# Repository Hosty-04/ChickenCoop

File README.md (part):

# Kurník

Systém pro automatizaci kurníku s detekcí snesených vajec - bakalářská práce

## Zadání

- Prostudujte možnosti automatizace uzavírání kurníku, možné metody detekce snesených vajec a dostupné možnosti komunikace a připojení zařízení do IoT sítě (např. NB-IoT, WiFi, LoRaWAN).
- Navrhněte systém pro automatické otevírání a uzavírání dvířek kurníku s možností rozšíření o jednotky se senzory ve snáškových hnízdech (min. 5 hnízd). Prostudujte možnosti napájení z akumulátoru nebo fotovoltaického panelu. Proveďte analýzu možnosti přenosu dat do cloudu a jejich zobrazení uživateli včetně historie snášek a možnosti vzdáleného ovládání, například skrze aplikaci.
- Na základě analýzy navrhněte způsob vzdálené uživatelské interakce pro zobrazení stavu dvířek, manuální ovládání a počítání snesených vajec.
- Navrhněte schéma zařízení, které bude obsahovat mikrořadič, komunikační modul, senzory, řízení dvířek, napájecí/nabíjecí obvody. Dbejte na nízký příkon celého zařízení. Proveďte návrh desky plošných spojů.
- Zkonstruujte hardwarovou realizaci navrženého systému. Osaďte a zprovozněte řídicí elektroniku. Vytvořte ovládací firmware. Realizujte přenos dat ze zařízení k uživateli včetně ovládacího rozhraní a možnosti zobrazení historie.
- Ověřte funkčnost systému experimentálním měřením a vyhodnoťte spolehlivost detekce a ovládání.
- Zveřejněte veškeré výrobní podklady na vhodné platformě (např. GitHub).

## Schémata

## Elektronika

<br>

<picture>
  <source media="(prefers-color-scheme: dark)" srcset="Schematics/block_schematic_electronics_white.png">
  <source media="(prefers-color-scheme: light)" srcset="Schematics/block_schematic_electronics_black.png">
  
</picture>

## Komunikace

<br>

<picture>
  <source media="(prefers-color-scheme: dark)" srcset="Schematics/block_schematic_comms_white.png">
  <source media="(prefers-color-scheme: light)" srcset="Schematics/block_schematic_comms_black.png">
  
</picture>

<br><br>

> Uživatelské příkazy cestují opačným směrem

## Popis

### 1) Mechanika

### a) Krabičky

Solární panel je uchycen v rámečku vytištěném z materiálu PETG, jehož vnější rozměr (360 × 240 mm) přesahuje rozměr panelu (340 × 220 mm) o 10 mm po každé straně. Tento materiál byl zvolen pro jeho vysokou houževnatost a teplotní odolnost. Kapsa pro panel je hluboká 4 mm, tedy o 1 mm více než tloušťka panelu, aby panel po vložení mírně zapadl pod úroveň okraje rámečku a nedocházelo k zadržování vody na jeho povrchu. Dno kapsy je opatřeno výřezem o rozměru 320 × 200 mm, odpovídajícím aktivní ploše panelu, takže rámeček má tvar pasparty a nestíní dopadající sluneční záření. Po vložení panelu do kapsy je spára mezi jeho okrajem a stěnou rámečku vyplněna venkovním UV odolným silikonovým tmelem, čímž vzniká vodotěsné a zároveň mechanicky pevné spojení bez nutnosti vrtat do samotného panelu. Rámeček je přišroubován přímo ke stěně kurníku vruty 6 × 80 mm s plastovými hmoždinkami 8 mm, a to přes čtyři otvory o průměru 5 mm v rozích mimo aktivní plochu panelu.

Konstrukce obsahuje jednu krabičku pro akumulátor o tloušťce stěny 2,4 mm a jednu krabičku (K) o tloušťce stěny 1,6 mm určenou pro mechaniku a elektroniku dvířek a hlavní mikrořadič. Pro každé snáškové hnízdo je dále vyhrazena samostatná krabička (Kx) se stejnou tloušťkou stěny, obsahující potřebnou elektroniku a hnízdový mikrořadič. Všechny krabičky jsou vytištěny na 3D tiskárně z materiálu PETG. Do tohoto materiálu je kvůli riziku deformace nutné vrtat při nízkých otáčkách. Zadní stěna krabiček je ve svislém směru prodloužena a má tloušťku 3,5 mm; v každém rohu této stěny jsou otvory pro vruty 4 × 40 mm, které umožňují upevnění krabiček k betonové stěně kurníku pomocí hmoždinek o průměru 6 mm. Víko je vytištěno samostatně s přesahem 2 mm; uprostřed jeho levé hrany je dutá trubička s vnitřním průměrem 2 mm. Stejná trubička je u všech krabiček na obou koncích vnější horní hrany levé stěny. Po vytištění je všemi třemi trubičkami protažen filament o průměru 1,75 mm, jehož konce se krátce nahřejí zapalovačem a roztepou do podoby hlaviček. Tím vzniká jednoduchý pant pro uchycení víka.

V krabičkách K a Kx jsou desky plošných spojů připevněny ke dnu pomocí montážních děr (hlavní i hnízdová deska po 3), šrouby vedou zeshora přes distanční sloupky a jsou zajištěny maticí. U víka krabiček jsou vytvořeny nízké drážky ve tvaru písmene U s mírně zaoblenými rohy, sloužící k protažení kabelů. Pro kabel o průřezu 1,5 mm² mají šířku 4,5 mm, hloubku 3 mm a zaoblení dna i hran 1 mm; pro kabel o průřezu 0,5 mm² šířku 3,5 mm, hloubku 2 mm a zaoblení dna i hran 0,75 mm; pro datový kabel pak šířku 6 mm, hloubku 3,5 mm a stejné zaoblení jako u prvního kabelu. Krabička pro akumulátor má zespodu dva kruhové otvory o průměru 5 mm určené pro průchod napájecích kabelů a dva větrací otvory o průměru 4 mm, umístěné v horní a spodní části tak, aby mohl uvnitř cirkulovat vzduch. Krabička Kx má zespodu jeden podlouhlý otvor 6 × 2 mm se zaoblenými konci pro průchod 4 vodičů plochého kabelu DS1058 s roztečí 1,27 mm, které prodlužují vodiče tenzometru (pásek 4 vodičů je široký 5,08 mm a tlustý asi 1 mm), krabička K pak ručně vyvrtaný a zakulacený otvor o průměru 4 mm pro lanko; anténa bude položená horizontálně uvnitř krabičky.

### b) Kabeláž

Pro připojení solárního panelu a akumulátoru je použita měděná ohebná licna o průřezu 1,5 mm², připojená přes 4pinovou pružinovou WAGO svorkovnici s roztečí 5,08 mm k desce plošných spojů. Tento průřez poskytuje dostatečnou proudovou rezervu při minimálním úbytku napětí. Stejným způsobem, avšak za využití licny o průřezu 0,5 mm², jsou k desce plošných spojů připojeny mikrospínače. Motor je u finální verze přes držák připevněn přímo k hlavní desce plošných spojů; u prototypu je připojen licnou o průřezu 0,5 mm² přes 2pinovou svorkovnici.

Pro datovou komunikaci byl zvolen kabel UTP CAT5e typu licna, jehož kroucené páry omezují rušení. K deskám plošných spojů je připojený přes konektory RJ45. Prodloužení vodičů tenzometru o průřezu 0,08 mm² zajišťují 4 vodiče plochého kabelu DS1058 (rozteč 1,27 mm) o stejné barvě a průřezu. Spojeny jsou pájkou a přes každý spoj je převlečena smršťovací bužírka s lepidlem o poměru 3:1 a rozměru 3 mm / 1 mm. K desce plošných spojů jsou připojeny přes 4pinovou pružinovou WAGO svorkovnici 233-504 s roztečí 2,54 mm (1 = E− (GND), 2 = E+ (AVDD), 3 = A− (IN−), 4 = A+ (IN+)).

Kabely a vodiče jsou vedeny v klasické elektroinstalační PVC liště o rozměrech 15 × 10 mm, upevněné k betonové stěně, respektive základové desce, pomocí vrutů 3 × 30 mm a hmoždinek o průměru 5 mm. Spoje jsou utěsněny akrylovým tmelem. Speciální UV odolná lišta není pro kabely vedené po venkovní stěně kurníku potřeba, protože tato stěna je vystavena slunci pouze při jeho západu. Životnost běžné lišty se odhaduje na 5–10 let.

U prototypu jsou využity stejné kabely, vodiče a svorkovnice. Na rozdíl od finální verze jsou ale využity drátky do nepájivého pole o průřezu 0,5 mm², který plně vyhovuje proudovému odběru systému.

### c) Konstrukce

Hlavní část systému je umístěna na vnější stěně kurníku, která splňuje požadavky na umístění solárního panelu popsané v kapitole Napájení. Toto řešení zjednodušuje montáž a zároveň z velké části eliminuje vliv amoniaku ze slepičího trusu na elektroniku.

Na betonovou stěnu jsou pomocí vrutů a hmoždinek připevněny svislé dřevěné hranolky, k jejichž bočním stěnám jsou vruty upevněny hliníkové U-profily se šířkou dna 15 mm, výškou bočních stěn 15 mm, tloušťkou 1,5 mm a délkou 1 m. První vrut je umístěn na horní pozici, nad kterou se dvířka nikdy nedostanou, a druhý vrut na dolní pozici, kam dvířka nikdy nedojedou. U-profily zajišťují přesné vedení dvířek při minimálním tření. V těchto profilech se ve svislém směru pohybují nalakovaná pěněná PVC dvířka o rozměrech 24 × 35 cm a tloušťce 8 mm (pozor na výrobní tolerance). Hmotnost těchto dvířek je 350 g. Při vrtání otvorů do PVC je nutné použít nízké otáčky a nevyvíjet nadměrný přítlak. Pěněné PVC bylo zvoleno pro nízkou hmotnost, odolnost proti vlhkosti a snadnou obrobitelnost.

V horní i dolní části hranolku jsou ve svislé ose zapuštěny dva pákové koncové spínače sledující polohu dvířek. Záhlubení široká 6,5 mm a vysoká 20 mm z vnitřní strany a 15 mm z vnější strany vedou skrz hranolek a 10 mm širokou hliníkovou drážku; z vnější strany jsou kabely vyvedeny přímo do lišty. Spínače jsou upevněny vruty o průměru 2 mm. Toto provedení představuje jednoduché řešení určování krajních poloh dvířek.

Na horní části přední strany dvířek je umístěno závěsné očko M5 z nerezové oceli A2, upevněné podložkou a samojistnou maticí ze stejného materiálu; očko prochází otvorem o průměru odpovídajícím jeho metrickému závitu. Očkem je protaženo syntetické lanko (zednická šňůra) o průměru 2 mm, zajištěné dračí smyčkou zakápnutou vteřinovým lepidlem. Syntetická šňůra nekoroduje, má nízkou průtažnost a je odolná vůči vlhkosti.

Lanko vede kolmo vzhůru do krabičky K, kde je navíjeno na špulku vytištěnou z materiálu PETG (šířka 2 cm, vnější průměr 2,5 cm). Lanko je provlečeno otvorem o průměru 3 mm na okraji špulky (na straně vzdálenější od motoru) a zajištěno osmičkovým uzlem, rovněž zakápnutým vteřinovým lepidlem; uzel je zapuštěn 8 mm hluboko do záhlubení o průměru 10 mm a lanko z něj vychází na okraji záhlubení směrem k okraji špulky.

Špulka má otvor s D-profilem (průměr 3 mm, hloubka 10 mm); pomocí stavěcího šroubu (červíku) M5 z nerezové oceli A4 (délka 6 mm) a mosazné závitové vložky M5 (délka 5,8 mm, průměr 7,1 mm) je upevněna na hřídeli nízkootáčkového (20 rpm) stejnosměrného motoru s kovovou převodovkou (6 V), a to ze strany, kde vstupuje lanko. Stejnosměrný motor s převodovkou byl zvolen místo krokového motoru, protože vystačí s jednoduchým budičem, převodovka mu dává vysoký krouticí moment a polohu dvířek určují koncové spínače, takže není potřeba počítat kroky. U finální verze bude motor přes držák připevněn k hlavní desce plošných spojů.

<br>

**Tah motoru pro různé krouticí momenty**

$$
M = F \cdot r
$$

$$
F_j = \frac{M_j}{r_s} = \frac{5\ \text{N·cm}}{12,5\ \text{mm}} = 4\ \text{N} \approx \mathbf{400\ \text{g tahu}}
$$

$$
F_d = \frac{M_d}{r_s} = \frac{4\ \text{N·cm}}{12,5\ \text{mm}} = 3,2\ \text{N} \approx \mathbf{320\ \text{g tahu}}
$$

$$
F_k = \frac{M_k}{r_s} = \frac{25\ \text{N·cm}}{12,5\ \text{mm}} = 20\ \text{N} \approx \mathbf{2\ \text{kg tahu}}
$$

kde:

- $F_j$ ... síla při jmenovitém krouticím momentu
- $F_d$ ... síla při doporučeném dlouhodobém trvalém zatížení
- $F_k$ ... síla při maximálním krátkodobém zatížení
- $M_j$ ... jmenovitý krouticí moment
- $M_d$ ... krouticí moment při doporučeném dlouhodobém trvalém zatížení
- $M_k$ ... krouticí moment při maximálním krátkodobém zatížení
- $r_s$ ... poloměr špulky

Dvířka o hmotnosti 350 g představují mírně vyšší zátěž, než je doporučené trvalé zatížení, tudíž lze očekávat pokles otáček motoru na 15–17 ot./min. Počítá se i s rezervou pro případ mírného drhnutí dvířek v drážkách. Nízkootáčkový motor spolu s menším vnějším průměrem špulky byl zvolen pro zvýšení síly motoru a snížení rizika přetrhnutí lanka nebo vykolejení dvířek.

<br>

Otvor pro mosaznou závitovou vložku má průměr 8 mm a v posledních 6,5 mm směrem ke hřídeli se zužuje na 6,5 mm. Vložka se do otvoru zavede pomocí 16mm šroubu M5; jakmile narazí na zúženou část otvoru, hlava šroubu se nahřeje mikropájkou, plast se v místě zúžení roztaví a umožní zalisování vložky. Po odejmutí pájky plast opět ztuhne a vložku pevně ukotví.

Vedlejší část systému tvoří spádovaná snášková hnízda s košíkem, orientovaná příčně ke stěně. Celá konstrukce musí být od stěny vzdálena natolik, aby se jí nikde nedotýkala a zároveň za ní zůstal prostor pro vedení kabelu. Návrh je koncipován tak, aby se do prostoru s tenzometrem nemohli dostat ani ti nejmenší hlodavci — rozměr základové desky a výška lišt jsou klíčové.

Pod hnízda je vruty (na vyšší straně hnízda přes dřevěné kvantlíky) připevněna voděodolná OSB 3 deska o rozměrech 37 × 28 cm a tloušťce 12 mm. Další deska (37-1,2-0,2 × 28-1,2-0,2 cm, stejná tloušťka) tvoří základovou desku a je připevněna k podlaze kurníku; třetí deska stejné tloušťky, o rozměrech 40 × 50 cm, slouží jako zadní stěna. Řezné hrany desek jsou natřeny lakem. Mezi horní a spodní deskou je u stěny umístěn tenzometr o tloušťce 12,7 mm, orientovaný kratší stranou s vodiči směrem ke stěně. Tenzometr váží s přesností 2 g, což pro vejce o hmotnosti 50–70 g plně postačuje, a je dimenzován na zatížení 20 kg — maximální předpokládané zatížení (dvě desky, hnízdo, dvě slepice a deset vajec) přitom činí přibližně 10 kg. Volný i pevný konec tenzometru je upevněn dvěma zápustnými imbusovými šrouby M5 z nerezové oceli A2, procházejícími vážicí, respektive základovou deskou skrz otvory o průměru 4,5 mm a zapuštěnými do záhlubení o průměru 10 mm a hloubce 3 mm; hlava šroubu je u vážicí desky zalita akrylovým tmelem. Použité šrouby mají délku 25 mm. Mezi deskami a závity tenzometru jsou umístěny distanční matice M6 z nerezové oceli A2 o tloušťce 4 mm.

Optická závora není pro počítání vajec v kurníku vhodná mimo jiné kvůli prachu, peří, podestýlce a zvědavým slepicím, jejichž přítomnost by mohla přerušit laserový paprsek a být chybně vyhodnocena jako propadnuté vejce. Z tohoto důvodu byl pro detekci vajec zvolen tenzometr.

Ze zbytku OSB desky jsou vyrobeny ochranné lišty, přišroubované zeshora po bocích základové desky. Lišty jsou vysoké 21,5 mm, protože vzdálenost mezi deskami činí 20,7 mm a celá horní konstrukce musí být podepřena pouze tenzometrem — zároveň musí zůstat zachována vůle alespoň 3 mm. Do zadní lišty je vyvrtán otvor, kterým prochází již prodloužený kabel od tenzometru; kabel nesmí být mechanicky namáhán tahem. Kabel dále vede vzhůru po stěně do krabičky Kx, odkud je z boku vyveden datový kabel, vedoucí vysoko po stěně až do krabičky K. Uprostřed konstrukce, naproti košíku, je vytvořen stavitelný doraz pomocí zápustného imbusového šroubu M5 z nerezové oceli A2 (délka 30 mm), procházejícího spodní deskou skrz otvor o průměru 4,5 mm a zapuštěného do záhlubení o průměru 10 mm a hloubce 6 mm. Doraz tvoří mosazná kloboučková matice M5 (délka 10 mm, délka závitu 7,5 mm), zvolená kvůli omezení ulpívání nečistot. Optimální vůle dorazu je 0,8 mm, což odpovídá jedné otáčce šroubu M5 nebo přibližně tloušťce běžné platební karty.

### 2) Řízení

Hlavní řídicí jednotkou systému je mikrořadič LoRa-E5 mini (M) se STM32WLE5JC a integrovaným LoRa modulem, komunikujícím přes LoRaWAN stack. Technologie LoRaWAN umožňuje na rozdíl od Wi-Fi komunikaci na velké vzdálenosti při nízké spotřebě energie a na rozdíl od NB-IoT trvalé řešení s dobrým pokrytím. U každého snáškového hnízda je umístěn úsporný mikrořadič STM32 NUCLEO-L031K6 (Mx); vlastní řadič v každém hnízdě zkracuje citlivé analogové vedení od tenzometru a usnadňuje přidání dalších hnízd. K programování slouží programátor ST-Link V2. Před programováním je potřeba programátor připojit k dané desce klasickými kabely DuPont — stačí propojit piny 3V3, SWCLK, SWDIO, GND a nRST. U finální verze jsou desky osazeny v paticích (dutinkových lištách); patice LoRa-E5 mini jsou vysoké 8,5 mm, takže pod modulem jsou na hlavní desce nízké SMD součástky a deska měří jen 81,5 × 40 mm. Stejně je řešena hnízdová deska: NUCLEO-L031K6 sedí v paticích 8,5 mm a pod ním jsou nízké SMD součástky. Vstupní konektor RJ45 je v levém horním rohu a vede kabel levou hranou, výstupní je v pravém horním rohu a vede kabel pravou hranou, svorkovnice tenzometru je u pravého okraje pod výstupním konektorem (horní hranou lícuje s horní hranou NUCLEO-L031K6) a deska měří 74 × 42 mm.

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
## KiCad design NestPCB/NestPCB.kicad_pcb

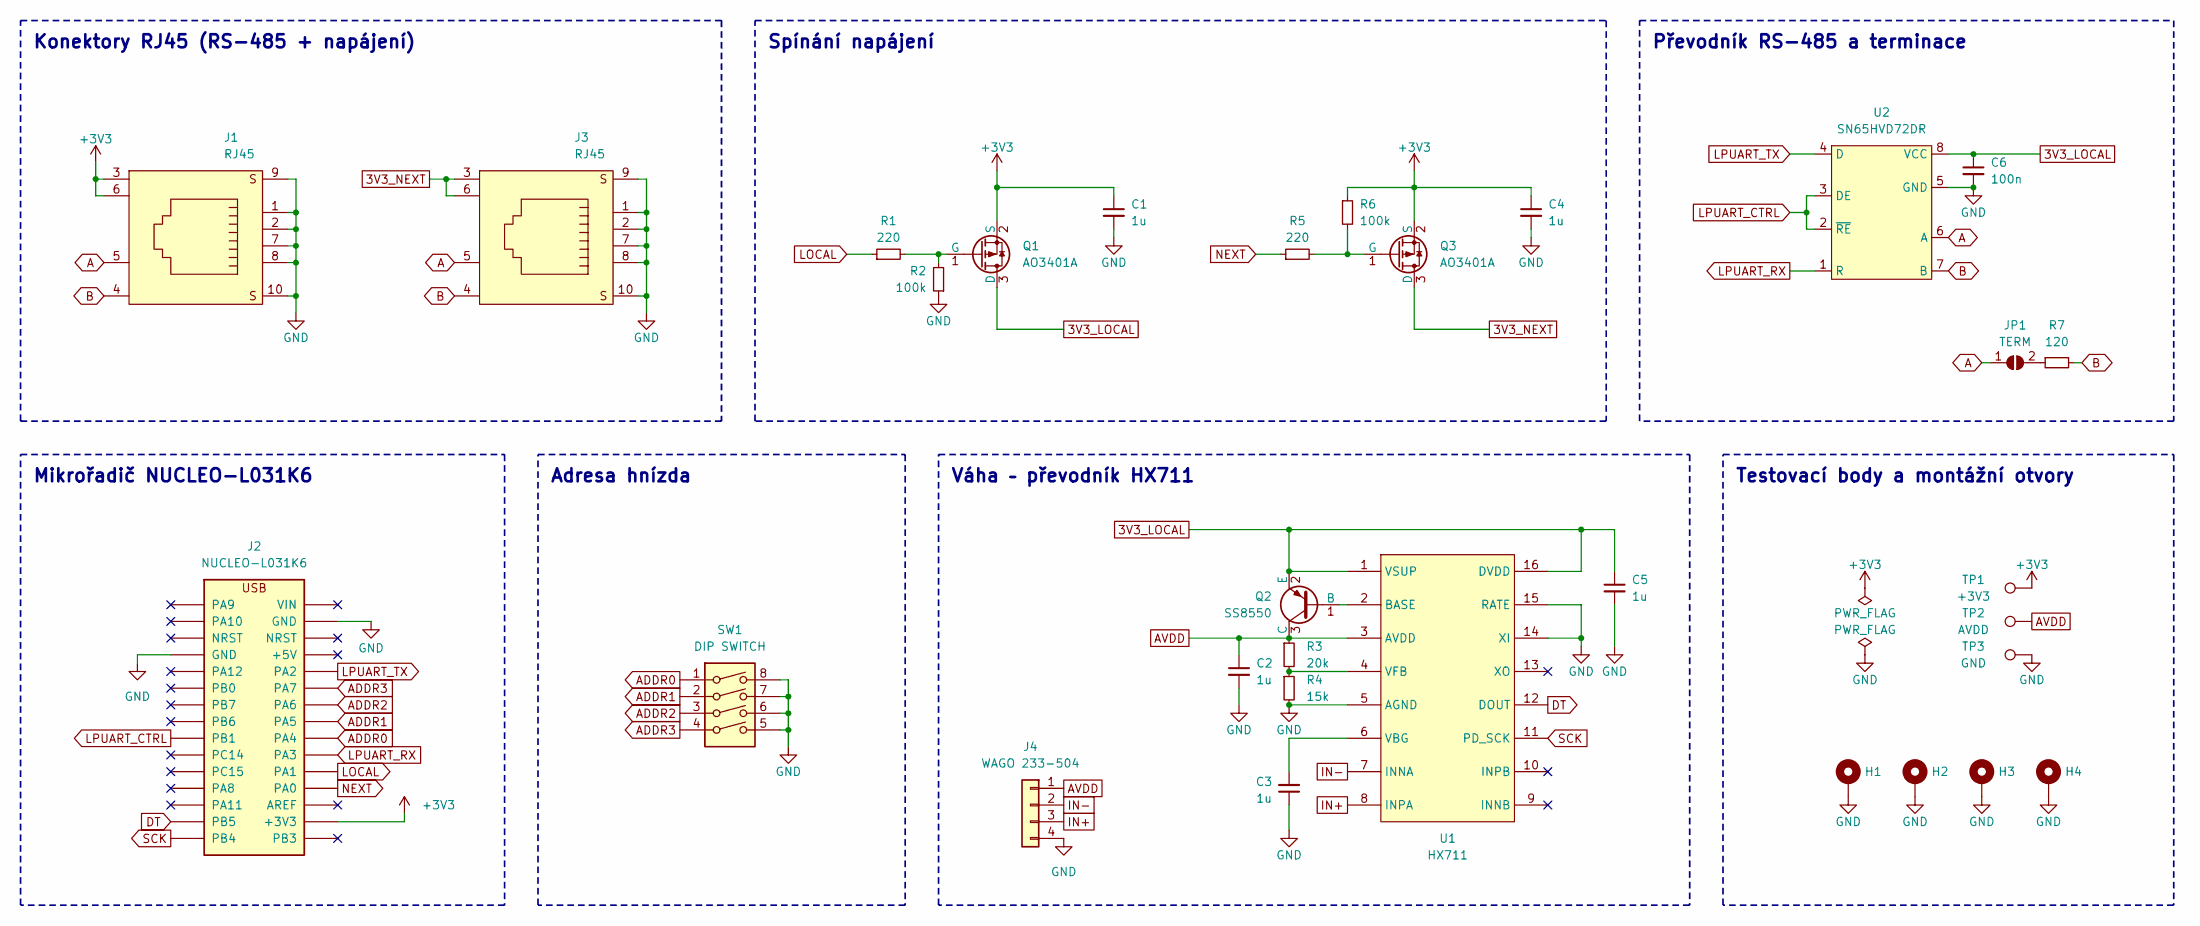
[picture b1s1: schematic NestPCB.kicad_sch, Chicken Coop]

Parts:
C1, C2, C3, C4, C5: 1u; C_0805_2012Metric
C6: 100n; C_0805_2012Metric
H1, H2, H3, H4: MountingHole_Pad; MountingHole_3.2mm_M3_Pad
J1, J3: RJ45; RJ45-TH_R-RJ45R08P-B000; LCSC Part C386756
J2: NUCLEO-L031K6
J4: WAGO 233-504; CONN-TH_233-504; LCSC Part C3309010
JP1: TERM; SolderJumper-2_P1.3mm_Open_RoundedPad1.0x1.5mm
Q1, Q3: AO3401A; SOT-23_L2.9-W1.3-P1.90-LS2.4-BR; LCSC Part C15127
Q2: SS8550; SOT-23_L2.9-W1.3-P1.90-LS2.4-BR; LCSC Part C8542
R1, R5: 220; R_0805_2012Metric
R2, R6: 100k; R_0805_2012Metric
R3: 20k; R_0805_2012Metric
R4: 15k; R_0805_2012Metric
R7: 120; R_0805_2012Metric
SW1: DIP SWITCH; SW-TH_DS-04XP; LCSC Part C319060
TP1: +3V3; TestPoint_THTPad_D2.0mm_Drill1.0mm
TP2: AVDD; TestPoint_THTPad_D2.0mm_Drill1.0mm
TP3: GND; TestPoint_THTPad_D2.0mm_Drill1.0mm
U1: HX711; SOP-16_L10.0-W3.9-P1.27-LS6.0-BL; LCSC Part C43656
U2: SN65HVD72DR; SOIC-8_L4.9-W3.9-P1.27-LS6.0-BL; LCSC Part C48125

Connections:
3V3_LOCAL: C5.1, C6.1, Q1.3 (D), Q2.2 (E), U1.1 (VSUP), U1.16 (DVDD), U2.8 (VCC)
3V3_NEXT: J3.3, J3.6, Q3.3 (D)
+3V3: C1.1, C4.1, J1.3, J1.6, J2.CN4-14 (+3V3), Q1.2 (S), Q3.2 (S), R6.1, TP1.1
A: J1.5, J3.5, JP1.1 (A), U2.6 (A)
ADDR0: J2.CN4-9 (PA4), SW1.1
ADDR1: J2.CN4-8 (PA5), SW1.2
ADDR2: J2.CN4-7 (PA6), SW1.3
ADDR3: J2.CN4-6 (PA7), SW1.4
AVDD: C2.1, J4.1, Q2.3 (C), R3.1, TP2.1, U1.3 (AVDD)
B: J1.4, J3.4, R7.2, U2.7 (B)
DT: J2.CN3-14 (PB5), U1.12 (DOUT)
GND: C1.2, C2.2, C3.1, C4.2, C5.2, C6.2, H1.1, H2.1, H3.1, H4.1, J1.1, J1.2, J1.7, J1.8, J1.9 (S), J1.10 (S), J2.CN3-4 (GND), J2.CN4-2 (GND), J3.1, J3.2, J3.7, J3.8, J3.9 (S), J3.10 (S), J4.4, R2.1, R4.2, SW1.5, SW1.6, SW1.7, SW1.8, TP3.1, U1.5 (AGND), U1.14 (XI), U1.15 (RATE), U2.5 (GND)
IN+: J4.3, U1.8 (INPA)
IN-: J4.2, U1.7 (INNA)
LOCAL: J2.CN4-11 (PA1), R1.1
LPUART_CTRL: J2.CN3-9 (PB1), U2.2 (~RE), U2.3 (DE)
LPUART_RX: J2.CN4-10 (PA3), U2.1 (R)
LPUART_TX: J2.CN4-5 (PA2), U2.4 (D)
NEXT: J2.CN4-12 (PA0), R5.1
unnamed: JP1.2 (B), R7.1
unnamed: Q1.1 (G), R1.2, R2.2
unnamed: Q2.1 (B), U1.2 (BASE)
unnamed: Q3.1 (G), R5.2, R6.2
unnamed: C3.2, U1.6 (VBG)
unnamed: R3.2, R4.1, U1.4 (VFB)
SCK: J2.CN3-15 (PB4), U1.11 (PD_SCK)

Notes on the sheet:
Váha – převodník HX711
Převodník RS-485 a terminace
Mikrořadič NUCLEO-L031K6
Testovací body a montážní otvory
Spínání napájení
Adresa hnízda
Konektory RJ45 (RS-485 + napájení)

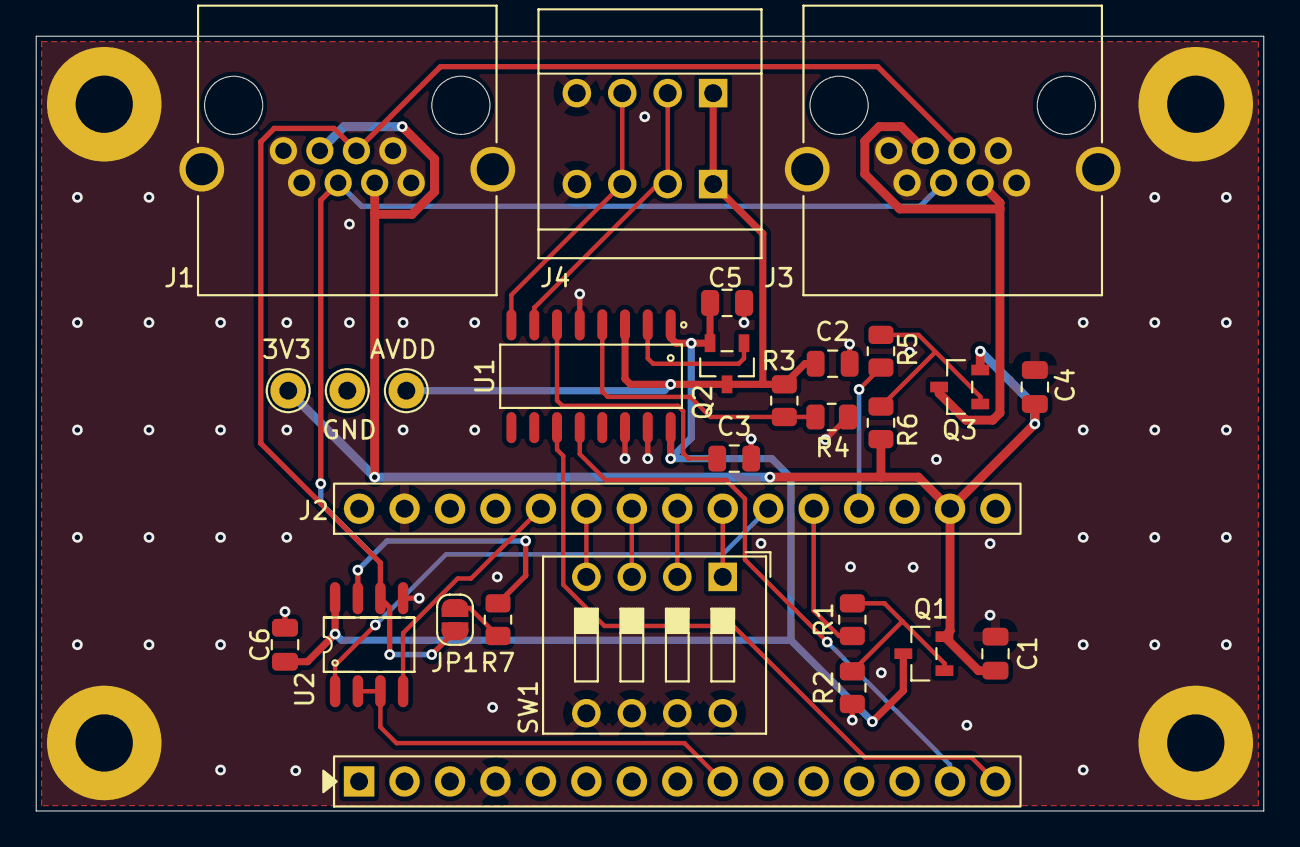
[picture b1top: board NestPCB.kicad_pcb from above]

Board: 2 copper layers, 68.6 x 43.3 mm, 31 parts (0 on the bottom side), 26 nets.

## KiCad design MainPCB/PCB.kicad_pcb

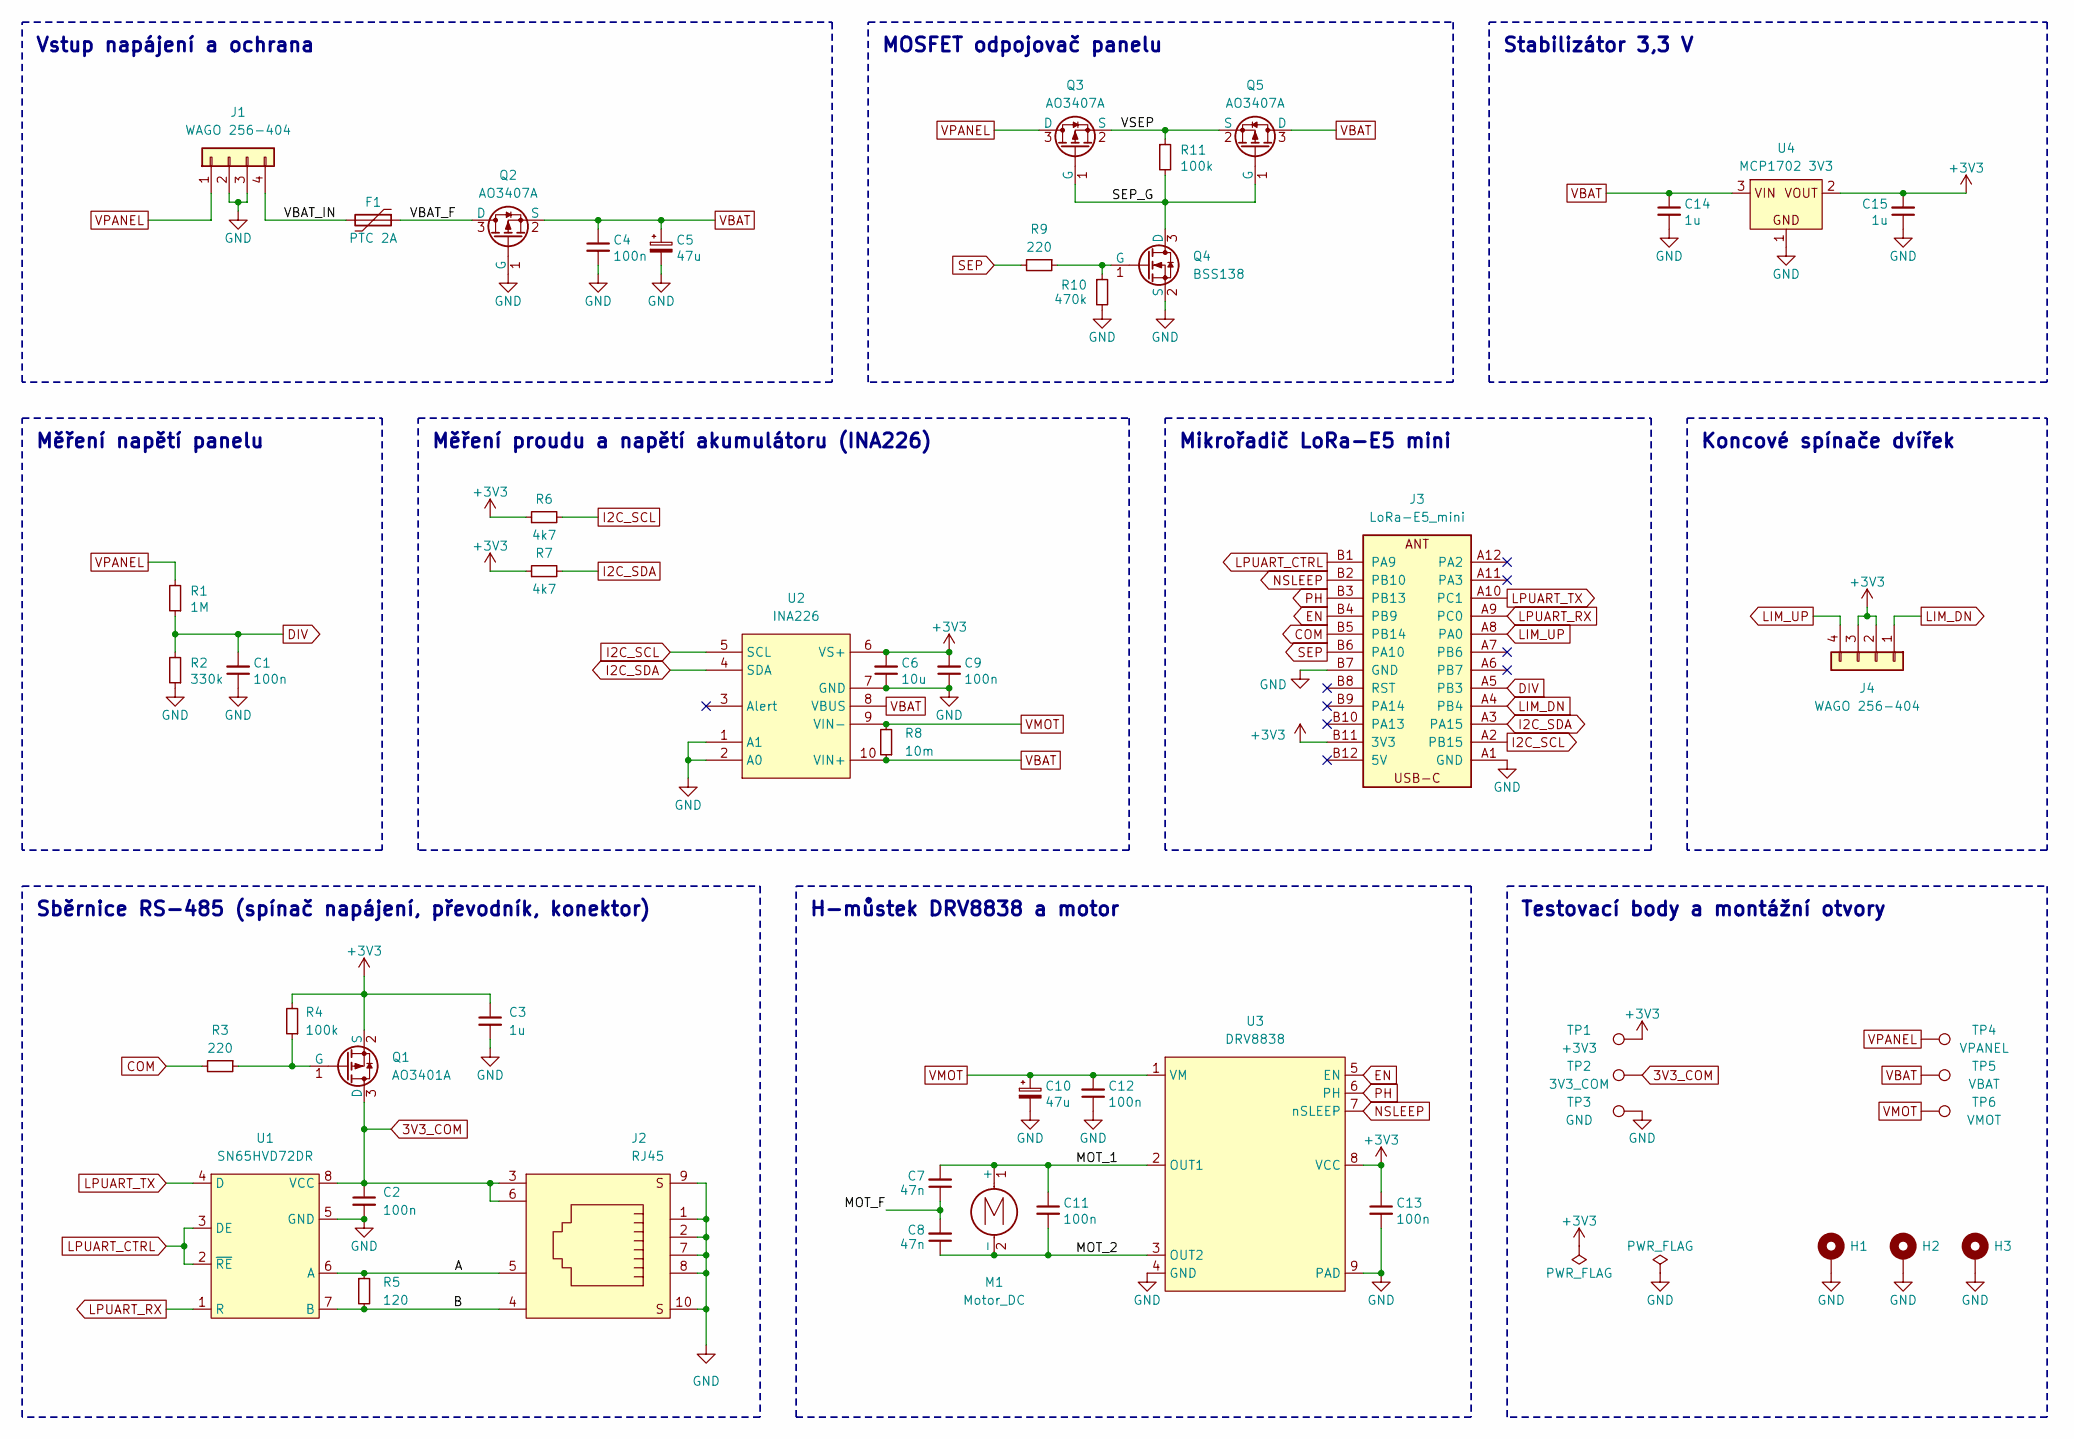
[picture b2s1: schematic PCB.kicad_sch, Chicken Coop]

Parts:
C1, C2, C4, C9, C11, C12, C13: 100n; C_0805_2012Metric
C3, C14, C15: 1u; C_0805_2012Metric
C5, C10: 47u; CP_Elec_6.3x5.8
C6: 10u; C_0805_2012Metric
C7, C8: 47n; C_0805_2012Metric
F1: PTC 2A; F1812; LCSC Part C545213
H1, H2, H3: MountingHole_Pad; MountingHole_3.2mm_M3_Pad
J1, J4: WAGO 256-404; CONN-TH_4P-P5.08-256-404; LCSC Part C3309374
J2: RJ45; RJ45-TH_R-RJ45R08P-B000; LCSC Part C386756
J3: LoRa-E5_mini
M1: Motor_DC; Pololu_MicroMotor_Bracket
Q1: AO3401A; SOT-23_L2.9-W1.3-P1.90-LS2.4-BR; LCSC Part C15127
Q2, Q3, Q5: AO3407A; SOT-23_L2.9-W1.3-P1.90-LS2.4-BR; LCSC Part C15155
Q4: BSS138; SOT-23_L2.9-W1.3-P1.90-LS2.4-BR; LCSC Part C52895
R1: 1M; R_0805_2012Metric
R2: 330k; R_0805_2012Metric
R3, R9: 220; R_0805_2012Metric
R4, R11: 100k; R_0805_2012Metric
R5: 120; R_0805_2012Metric
R6, R7: 4k7; R_0805_2012Metric
R8: 10m; R_1206_3216Metric
R10: 470k; R_0805_2012Metric
TP1: +3V3; TestPoint_THTPad_D2.0mm_Drill1.0mm
TP2: 3V3_COM; TestPoint_THTPad_D2.0mm_Drill1.0mm
TP3: GND; TestPoint_THTPad_D2.0mm_Drill1.0mm
TP4: VPANEL; TestPoint_THTPad_D2.0mm_Drill1.0mm
TP5: VBAT; TestPoint_THTPad_D2.0mm_Drill1.0mm
TP6: VMOT; TestPoint_THTPad_D2.0mm_Drill1.0mm
U1: SN65HVD72DR; SOIC-8_L4.9-W3.9-P1.27-LS6.0-BL; LCSC Part C48125
U2: INA226; MSOP-10_L3.0-W3.0-P0.50-LS5.0-BL; LCSC Part C49851
U3: DRV8838; WSON-8_L2.0-W2.0-P0.50-TL-EP; LCSC Part C86667
U4: MCP1702 3V3; SOT-23_L2.9-W1.3-P1.90-LS2.4-BR; LCSC Part C33844

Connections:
3V3_COM: C2.1, J2.3, J2.6, Q1.3 (D), TP2.1, U1.8 (VCC)
+3V3: C3.1, C6.2, C9.2, C13.1, C15.2, J3.B11 (3V3), J4.2, J4.3, Q1.2 (S), R4.2, R6.1, R7.1, TP1.1, U2.6 (VS+), U3.8 (VCC), U4.2 (VOUT)
/A: J2.5, R5.1, U1.6 (A)
/B: J2.4, R5.2, U1.7 (B)
/MOT_1: C7.2, C11.1, M1.1 (+), U3.2 (OUT1)
/MOT_2: C8.1, C11.2, M1.2 (-), U3.3 (OUT2)
/SEP_G: Q3.1 (G), Q4.3 (D), Q5.1 (G), R11.2
/VBAT_F: F1.1, Q2.3 (D)
/VBAT_IN: F1.2, J1.4
/VSEP: Q3.2 (S), Q5.2 (S), R11.1
COM: J3.B5 (PB14), R3.2
DIV: C1.2, J3.A5 (PB3), R1.1, R2.2
EN: J3.B4 (PB9), U3.5 (EN)
GND: C1.1, C2.2, C3.2, C4.2, C5.2, C6.1, C9.1, C10.2, C12.1, C13.2, C14.2, C15.1, H1.1, H2.1, H3.1, J1.2, J1.3, J2.1, J2.2, J2.7, J2.8, J2.9 (S), J2.10 (S), J3.A1 (GND), J3.B7 (GND), Q2.1 (G), Q4.2 (S), R2.1, R10.2, TP3.1, U1.5 (GND), U2.1 (A1), U2.2 (A0), U2.7 (GND), U3.4 (GND), U3.9 (PAD), U4.1 (GND)
I2C_SCL: J3.A2 (PB15), R6.2, U2.5 (SCL)
I2C_SDA: J3.A3 (PA15), R7.2, U2.4 (SDA)
LIM_DN: J3.A4 (PB4), J4.1
LIM_UP: J3.A8 (PA0), J4.4
LPUART_CTRL: J3.B1 (PA9), U1.2 (~RE), U1.3 (DE)
LPUART_RX: J3.A9 (PC0), U1.1 (R)
LPUART_TX: J3.A10 (PC1), U1.4 (D)
NSLEEP: J3.B2 (PB10), U3.7 (nSLEEP)
unnamed: C7.1, C8.2
unnamed: Q1.1 (G), R3.1, R4.1
unnamed: Q4.1 (G), R9.1, R10.1
PH: J3.B3 (PB13), U3.6 (PH)
SEP: J3.B6 (PA10), R9.2
VBAT: C4.1, C5.1, C14.1, Q2.2 (S), Q5.3 (D), R8.1, TP5.1, U2.8 (VBUS), U2.10 (VIN+), U4.3 (VIN)
VMOT: C10.1, C12.2, R8.2, TP6.1, U2.9 (VIN-), U3.1 (VM)
VPANEL: J1.1, Q3.3 (D), R1.2, TP4.1

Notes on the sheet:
Mikrořadič LoRa-E5 mini
H-můstek DRV8838 a motor
Testovací body a montážní otvory
MOSFET odpojovač panelu
Měření napětí panelu
Koncové spínače dvířek
Stabilizátor 3,3 V
Vstup napájení a ochrana
Sběrnice RS-485 (spínač napájení, převodník, konektor)
Měření proudu a napětí akumulátoru (INA226)

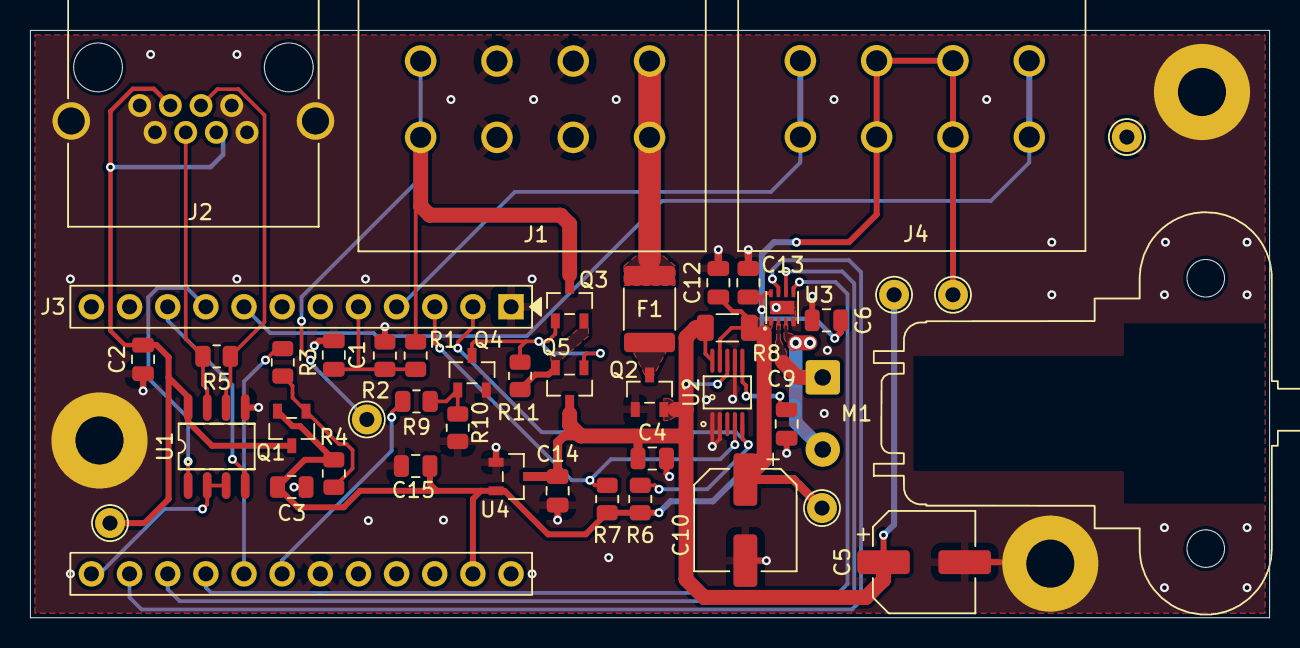
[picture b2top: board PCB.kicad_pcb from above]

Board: 2 copper layers, 82.5 x 39.1 mm, 47 parts (0 on the bottom side), 29 nets.

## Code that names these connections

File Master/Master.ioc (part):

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Mcu.Name=STM32WLE5JCIx
Mcu.Package=UFBGA73
Mcu.UserName=STM32WLE5JCIx
PA0.GPIOParameters=GPIO_Label
PA0.GPIO_Label=LIM_UP
PA0.Signal=GPIO_Analog
PA10.GPIOParameters=PinState,GPIO_Label
PA10.GPIO_Label=SEP
PA10.PinState=GPIO_PIN_SET
PA10.Signal=GPIO_Output
PA13.GPIOParameters=GPIO_Label
PA13.GPIO_Label=DEBUG_SWDIO
PA13.Mode=Serial_Wire
PA13.Signal=DEBUG_JTMS-SWDIO
PA14.GPIOParameters=GPIO_Label
PA14.GPIO_Label=DEBUG_SWCLK
PA14.Mode=Serial_Wire
PA14.Signal=DEBUG_JTCK-SWCLK
PA15.GPIOParameters=GPIO_Label
PA15.GPIO_Label=I2C_SDA
PA15.Mode=I2C
PA15.Signal=I2C2_SDA
PA2.GPIOParameters=GPIO_Label
PA2.GPIO_Label=USART_TX
PA2.Mode=Asynchronous
PA2.Signal=USART2_TX
PA3.GPIOParameters=GPIO_Label
PA3.GPIO_Label=USART_RX
PA3.Mode=Asynchronous
PA3.Signal=USART2_RX
PA4.GPIOParameters=GPIO_Label
PA4.GPIO_Label=RF_CTRL1
PA4.Signal=GPIO_Output
PA5.GPIOParameters=GPIO_Label
PA5.GPIO_Label=RF_CTRL2
PA5.Signal=GPIO_Output
PA9.GPIOParameters=GPIO_Label
PA9.GPIO_Label=LPUART_CTRL
PA9.Signal=GPIO_Analog
PB0-VDD_TCXO.Mode=HSE-TCXO
PB0-VDD_TCXO.Signal=VDDTCXO
PB10.GPIOParameters=GPIO_Label
PB10.GPIO_Label=NSLEEP
PB10.Signal=GPIO_Analog
PB13.GPIOParameters=GPIO_Label
PB13.GPIO_Label=PH
PB13.Signal=GPIO_Analog
PB14.GPIOParameters=PinState,GPIO_Label
PB14.GPIO_Label=COM
PB14.PinState=GPIO_PIN_SET
PB14.Signal=GPIO_Output
PB15.GPIOParameters=GPIO_Label
PB15.GPIO_Label=I2C_SCL
PB15.Mode=I2C
PB15.Signal=I2C2_SCL
PB3.GPIOParameters=GPIO_Label
PB3.GPIO_Label=DIV
PB3.Mode=IN2
PB3.Signal=ADC_IN2
PB4.GPIOParameters=GPIO_Label
PB4.GPIO_Label=LIM_DN
PB4.Signal=GPIO_Analog
PB9.GPIOParameters=GPIO_Label
PB9.GPIO_Label=EN
PB9.Signal=S_TIM17_CH1
PC0.GPIOParameters=GPIO_Label
PC0.GPIO_Label=LPUART_RX
PC0.Mode=Asynchronous
PC0.Signal=LPUART1_RX
PC1.GPIOParameters=GPIO_Label
PC1.GPIO_Label=LPUART_TX
PC1.Mode=Asynchronous
PC1.Signal=LPUART1_TX
PC14-OSC32_IN.Mode=LSE-External-Oscillator
PC14-OSC32_IN.Signal=RCC_OSC32_IN
PC15-OSC32_OUT.Mode=LSE-External-Oscillator
PC15-OSC32_OUT.Signal=RCC_OSC32_OUT
RCC.HSE_VALUE=32000000
RCC.SYSCLKFreq_VALUE=48000000
RCC.SYSCLKSource=RCC_SYSCLKSOURCE_PLLCLK
board=custom

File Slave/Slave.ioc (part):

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Mcu.Name=STM32L031K(4-6)Tx
Mcu.Package=LQFP32
Mcu.UserName=STM32L031K6Tx
PA0.GPIOParameters=PinState,GPIO_Label
PA0.GPIO_Label=NEXT
PA0.PinState=GPIO_PIN_SET
PA0.Signal=GPIO_Output
PA1.GPIOParameters=GPIO_Label
PA1.GPIO_Label=LOCAL
PA1.Signal=GPIO_Output
PA13.Mode=Serial_Wire
PA13.Signal=SYS_SWDIO
PA14.Mode=Serial_Wire
PA14.Signal=SYS_SWCLK
PA2.GPIOParameters=GPIO_Label
PA2.GPIO_Label=LPUART_TX
PA2.Mode=Asynchronous
PA2.Signal=LPUART1_TX
PA3.GPIOParameters=GPIO_PuPd,GPIO_Label
PA3.GPIO_Label=LPUART_RX
PA3.GPIO_PuPd=GPIO_PULLUP
PA3.Mode=Asynchronous
PA3.Signal=LPUART1_RX
PA4.GPIOParameters=GPIO_Label
PA4.GPIO_Label=ADDR0
PA4.Signal=GPIO_Analog
PA5.GPIOParameters=GPIO_Label
PA5.GPIO_Label=ADDR1
PA5.Signal=GPIO_Analog
PA6.GPIOParameters=GPIO_Label
PA6.GPIO_Label=ADDR2
PA6.Signal=GPIO_Analog
PA7.GPIOParameters=GPIO_Label
PA7.GPIO_Label=ADDR3
PA7.Signal=GPIO_Analog
PB1.GPIOParameters=GPIO_Label
PB1.GPIO_Label=LPUART_CTRL
PB1.Mode=Hardware Flow Control (RS485)
PB1.Signal=LPUART1_DE
PB4.GPIOParameters=GPIO_Label
PB4.GPIO_Label=SCK
PB4.Signal=GPIO_Output
PB5.GPIOParameters=GPIO_Label
PB5.GPIO_Label=DT
PB5.Signal=GPIO_Input
RCC.HSE_VALUE=8000000
RCC.SYSCLKFreq_VALUE=2097000
board=custom
